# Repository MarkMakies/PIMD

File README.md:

# PIMD — Pulse Induction Metal Detector

*A from-scratch, multi-band pulse-induction metal detector built for autonomous, position-tagged ground survey.*

> Above: a single live frame with a steel spanner **and** a copper pipe under the coil. The two
> materials separate *spatially* inside the decay-space matrix — non-ferrous (blue) collapses early,
> ferrous (red) persists late. Getting that separation out of a pulse-induction detector is the whole point.

**Up to date Build diary:** <https://makies.com.au/pulse-induction-metal-detector/>

---

## What it is

A pulse-induction (PI) metal detector designed and built from scratch since November 2023 by a maker
with no prior analogue-electronics background. It is **not** a clone — several design choices are
deliberately unconventional.

In the language of the field, it's a **low-cost, monostatic time-domain electromagnetic (TEM)
spectrometer doing cued interrogation** — though it started life as nothing more ambitious than
"let's build a metal detector with no experience." It is one payload of a larger system: the coil is
towed on a trailer behind **Roverling**, an autonomous RTK-GPS ground robot, so every detection event
can be tagged with centimetre-level position and streamed back over LoRa. It therefore has to be
*quiet, stable and remotely controllable*, not merely sensitive.

What makes it unusual among PI detectors is that it doesn't optimise a single operating point.
It cycles through a user-defined grid of operating points and reports, for every frame, a
two-dimensional **decay-space matrix** — frequency/pulse-width on one axis, decay-amplitude (time) on
the other — that is designed from the ground up as an input to a classifier.

## How it works (in brief)

A high-current pulse energises the TX coil; on hard cutoff the collapsing field produces a flyback
and then a decaying eddy-current response. A nearby target perturbs that decay. The conditioned RX
signal is sampled at precise, calibrated delays.

- **Mode 1** — a single filtered (32-bit) sample at one held delay: the low-noise telemetry path, used for baselines and field tests.
- **Mode 2** — an interleaved sweep across a profile of *(frequency, pulse-width, sample-delay)* points, reported as one frame per sweep. The grid is not fixed by the hardware, and it has deliberately *narrowed* as the corpus taught which cells earn their place. The July 2026 signature corpus was captured on a **63-cell** grid (7 pulse widths × 9 delays, spaced geometrically 9 → 100 µs at ×1.5 per step). The **current profile, `cal_2x11_v5`, runs 2 pulse widths (10 and 100 µs) × 11 sample delays = a 22-cell matrix**, sweeping at **16.1 Hz** *(measured)* — ~30% faster frames for the loss of the redundant middle bands. It is **not yet locked and has no corpus behind it**. Repetition rates are chosen to hold duty near 30%; the 100 µs band runs at 3.125 kHz and **requires the cooling fan** (see Hardware).
- Sample delays use **two anchoring schemes in one profile**, where a PI profile conventionally picks one. Early cells are **amplitude-anchored** to a ladder of voltages (**2.4 V → 125 mV**) high on the flyback decay rather than the usual bottom ~700 mV — that region carries the most discrimination information, and it is where target *polarity* separates the families. Late cells are **time-anchored** on a geometric ladder out along the tail, because past the front end's lobe both families read positive and only *decay rate* separates them. Every delay is snapped to the 8 ns PWM grid (off-grid requests are silently rounded by the hardware). The profile spans the decay from 2.4 V down to the ~110 mV pedestal with no gaps — the null minimum is sampled deliberately, not avoided.
- **Polarity convention:** ferrous targets read **positive** (stored magnetic energy reinforces the decay); non-ferrous read **negative** (opposing eddy currents weaken it). A third class turns out to be common in practice: **crossover targets** (cast iron, some stainless, real jewelry with steel fittings) read negative at short pulses and positive at long ones — the pulse-width axis resolves what a single operating point would misclassify.

## Highlights

- A multi-band decay-space matrix recovering **multi-time-constant discrimination from a PI platform** — something most commercial PI detectors don't attempt.
- **Validated on a 17-target labelled corpus** (July 2026): signature *shape* is invariant with target distance (5–15 cm, 30× amplitude range) and repeats across sessions and recalibrations to within a few percent — the property the classification layer is built on.
- Targets fall into **three shape families** — ferrous, non-ferrous, and crossover — and overlapping targets combine **linearly** (a spanner + copper pipe frame decomposes back into its parts at 0.99 correlation), so unmixing is on the table, not just classification.
- Phase-locked TX/sample timing on one RP2040 PWM slice — **~5 ns sample-trigger jitter (measured)**.
- LTC2508-32 dual-output front end (filtered 32-bit + raw 14-bit no-latency).
- A dedicated delay-calibration tool that measures the clip-release point per band and exports calibrated profiles.
- Three PyQt6 desktop tools: live Mode 1 GUI, the Mode 2 heatmap + ML-data bridge (`ClassViz`, including a self-describing session recorder for training data), and the delay calibrator.
- Built for autonomous use: RTK-GPS position tagging, LoRa telemetry, single dedicated low-noise supply.

## Repository layout

```
README.md                  This file — start here
DESIGN.md                  Full engineering reference (hardware, firmware, protocol, test log)
CHANGELOG.md               Project change log
CLAUDE.md                  Contributor / agent conventions (version bumps, changelog discipline)

mcu/                       MicroPython firmware for the RP2040-Zero
  pimd_mcu.py  main.py

src/                       PC-side tools (PyQt6)
  pimd_gui.py              Mode 1 filtered-telemetry GUI
  pimd_classviz.py         Mode 2 decay-space heatmap + ML logger
  pimd_delaycal.py         Delay-calibration sweep tool
  pimd_rawlog.py           Raw Mode 2 session logger
  pimd_pack.py             Shared 6S pack fuel-gauge maths (imported by the four GUI apps)
  pimd_shape.py            Shared feature maths (family / crossing / decay persistence)
  pimd_features.py         Training-corpus builder
  pimd_target_check.py     Target-registry validator
  pimd_corpus_check.py     Corpus-level acceptance checker
  requirements.txt
  data/                    Settings, captured CSVs and calibrated profiles (runtime-generated)

Electronics/PIMD604/       KiCad project — schematic rev 6.04 (as-built)

References/                Schematic export, scope captures, sample heatmaps
```

## Toolchain & workflow

The firmware is the measurement primitive; every PC tool is a client of the same USB-serial
protocol (`DESIGN.md` §9). Together they form one pipeline:

```
mcu/pimd_mcu.py (RP2040)            — the measurement primitive
      │  USB-serial, ASCII records (DESIGN §9)
      ├─► src/pimd_delaycal.py      — calibrates sample delays,
      │        exports cal_*.json profiles ──► src/data/profiles/
      ├─► src/pimd_gui.py           — Mode 1 live telemetry / bench monitor
      ├─► src/pimd_rawlog.py        — verbatim Mode 2 session logger (ground truth)
      └─► src/pimd_classviz.py      — Mode 2 heatmap; loads & runs saved profiles;
               │    captures signatures ──► src/data/corpora/ + src/data/sessions/
               └─ uses src/pimd_shape.py — shared feature maths
                            │
                            ▼
          src/pimd_features.py + src/pimd_target_check.py
               — registry-validated training-corpus builder ──► ML corpus
```

`pimd_pack.py` is shared by all four GUI apps, so they can never disagree about the same battery.

**Typical workflow**

1. Flash the firmware once (`DESIGN.md` §16).
2. Run **delaycal** after a full thermal soak to produce a calibrated profile; lock the profile JSON.
3. Run **classviz**, *Load & Run* the locked profile, and capture target signatures against the
   target registry in `src/data/targets/`.
4. Build the corpus with **features**; gate a capture day with **corpus_check**.

**gui** is the independent Mode 1 bench monitor used for noise-floor and drift investigation at a
single operating point. **rawlog** is the deliberately dumb recorder: it writes every line the
firmware sends, verbatim, so there is always a raw record no display logic can corrupt. Never run
Mode 1 and Mode 2 at once — always send `E` between mode switches.

> Each tool carries its own detailed operating notes — intent, wire commands used, record formats
> and per-version lineage — in its **file header**, which is updated in the same edit that changes
> the behaviour. Current firmware and tool versions, and the operating profile in use, are on the
> header line at the top of **`DESIGN.md`**; they are deliberately not duplicated here.

## Quick start

No build step for either the PC tools or the firmware.

### PC tools

```bash
python3 -m venv .venv && source .venv/bin/activate
pip install -r src/requirements.txt
cd src
python pimd_gui.py        # Mode 1 GUI (filtered telemetry)
python pimd_classviz.py   # Mode 2 decay-space visualiser + ML bridge
python pimd_delaycal.py   # delay-calibration sweep
```

The tools connect to the board on `/dev/ttyACMx` at 115200 baud.

### Firmware

```bash
# No build step — copy onto the board, then power-cycle it.
.venv/bin/mpremote connect /dev/ttyACM0 fs cp mcu/pimd_mcu.py :pimd_mcu.py + fs cp mcu/main.py :main.py
# (mpremote reset does not re-enumerate USB reliably — power-cycle the board.)
.venv/bin/mpremote connect /dev/ttyACM0 repl
```

### Bench-test over a serial terminal (115200)

```
V                              identify / firmware version
L                              list profiles
Q5   then  G                   Mode 2: stream the loaded operating profile (W5 records);  E to stop
*5000,40000,8400,256  then S   Mode 1: stream (* records, ~20/s);  E to stop
A32                            one 32-sample boxcar average (R record)
```

> Protocol note (firmware v4.23+): the `*` command takes **freq in Hz, pulse/delay in ns**; the `D`
> dynamic-profile command takes **µs**. See `DESIGN.md` §9 for the full contract.

## Hardware

- **Schematic:** the published KiCad project is **rev 6.04**, which represents the board **as-built**. The PCB itself was fabricated from rev **6.01**; 6.04 captures the corrections — there were a few PCB issues that needed rectifying after manufacture.
- **Front end / drive:** functional but a known rework target — a future revision will replace the TX switch and gate driver (planned: STP10NM60N + TC4420/TC4429) to retire the current FET being run past its rated SOA.
- **Thermal:** a thermistor is now fitted to the TX damping resistor. Thermal drift settles to effectively zero once the resistor reaches ~80 °C, which is the dominant warm-up transient.

## Roadmap

This release is **Phase 2 — publish the work to date.** Active and planned work:

- **Phase 3 — machine learning.** Use the decay-space matrix for filtering, classification and (the stretch goal) ground discrimination. First milestone reached (July 2026): a locked, delay-calibrated operating profile and a 17-target labelled signature corpus recorded at three distances, with distance-invariance, cross-session repeatability and mixture linearity all verified in air.
- **Faster response.** First cut made (August 2026): 63 cells → 22, for ~30% faster sweeps. Because the corpus says different targets go redundant in *different* cells, the narrowed grid has to earn its keep against a fresh corpus before it can be locked — that re-validation is the open work, along with per-cell averaging.
- **Front-end revision** (TX switch + gate driver, as above), plus a scope measurement of TX coil current vs pulse width to settle whether the longest band is past the coil-current plateau.

See **DESIGN.md §14** for the full open-problems list.

## Documentation

- **[DESIGN.md](DESIGN.md)** — the complete engineering reference: measured operating envelope, coils, drive and receive chains, timing, serial protocol, power, invariants and curated test log. Self-contained; a new reader (human or agent) can pick up the project cold from it.
- **Per-app notes** — each tool's intent, operation, wire commands and version lineage live in its own **file header** (`mcu/pimd_mcu.py`, `src/pimd_*.py`); the pipeline that connects them is under *Toolchain & workflow* above.
- **Build diary** — the full chronological story, with photos and dead-ends: <https://makies.com.au/pulse-induction-metal-detector/>
- **Video** — <https://www.youtube.com/@markmakies>

## Licence

This project uses two licences, matched to the kind of work:

- **Code** (`src/`, `mcu/`) — **GNU GPL v3.0-or-later**. See [`LICENSE`](LICENSE).
- **Hardware and documentation** (`Electronics/`, `DESIGN.md`, schematics, images) — **Creative Commons Attribution-ShareAlike 4.0 (CC BY-SA 4.0)**. See [`LICENSE-docs`](LICENSE-docs).

Pulse Induction Metal Detector © 2022–2026 Mark Makies.

## Author

Built by **Mark Makies** (Australia).
Find more work at <https://makies.au/>.

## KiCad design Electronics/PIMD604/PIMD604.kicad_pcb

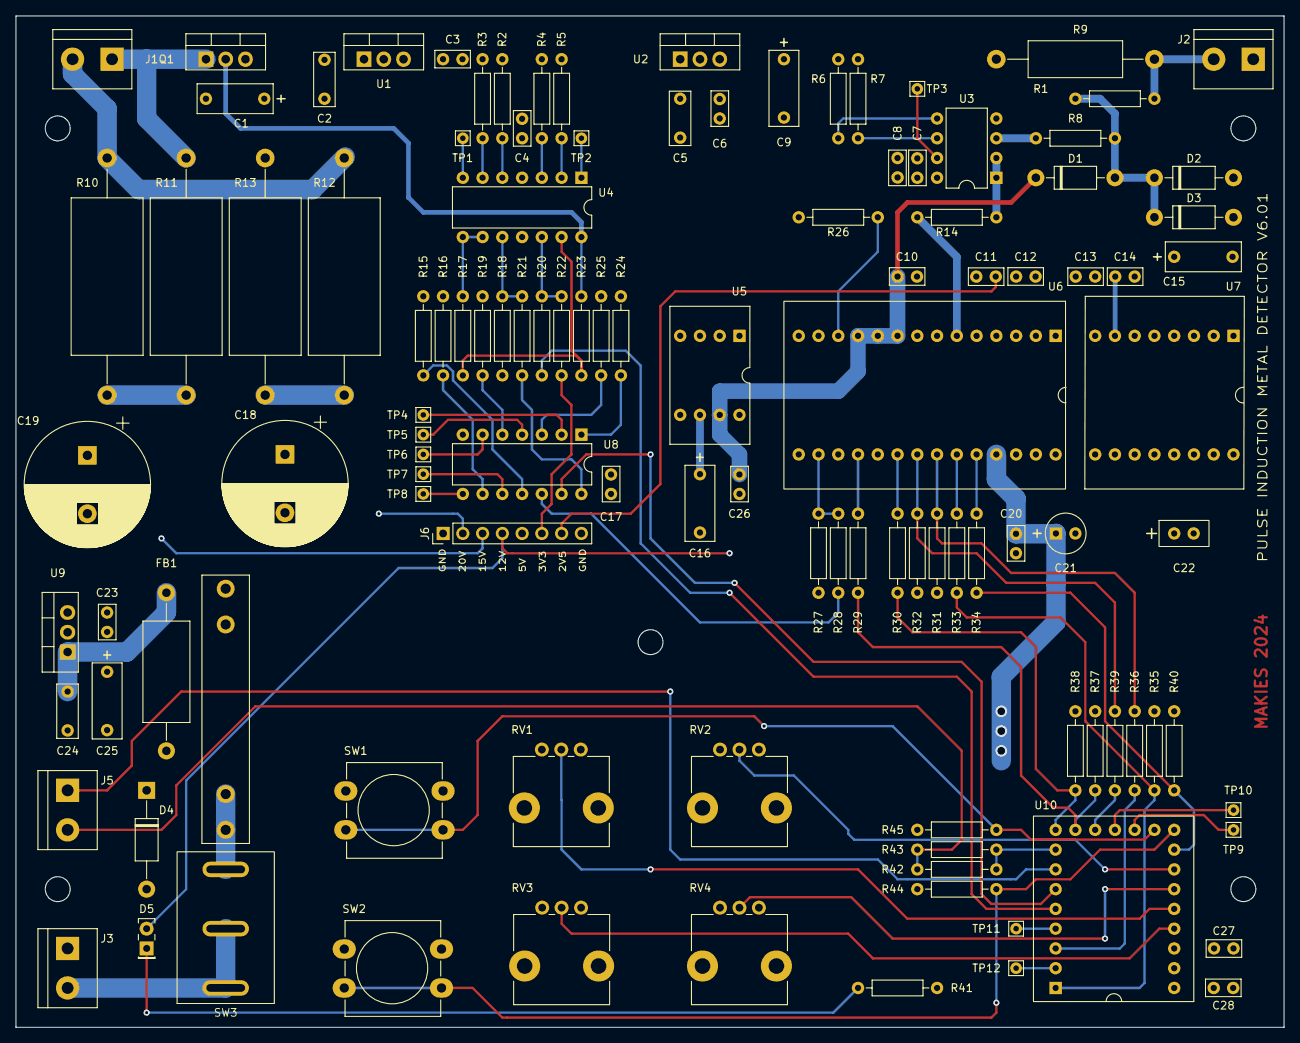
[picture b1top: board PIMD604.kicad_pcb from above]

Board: 4 copper layers, 163.0 x 130.0 mm, 120 parts (0 on the bottom side), 77 nets.

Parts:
C1, C9, C15, C16, C25: 47u; C_Rect_L9.0mm_W3.6mm_P7.50mm_MKT
C2, C5, C24: 220n; C_Disc_D5.0mm_W2.5mm_P5.00mm
C3, C4, C6, C8, C10, C11, C13, C17, C20, C23, C26, C27, C28: 100n; C_Disc_D3.0mm_W2.0mm_P2.50mm
C7, C12, C14: 10n; C_Disc_D3.0mm_W2.0mm_P2.50mm
C18: 2200u; CP_Radial_D16.0mm_P7.50mm
C19: 4700u; CP_Radial_D16.0mm_P7.50mm
C21: 10u; CP_Radial_Tantal_D5.0mm_P2.50mm
C22: 4u7; C_Rect_L7.0mm_W3.5mm_P2.50mm_P5.00mm
D1, D3: 1N5817; D_DO-41_SOD81_P10.16mm_Horizontal
D2: 1N4733; D_DO-41_SOD81_P10.16mm_Horizontal
D4: 1N4004; D_DO-41_SOD81_P12.70mm_Horizontal
D5: LED; LED_Rectangular_W5.0mm_H2.0mm
F1: 2A; Fuseholder_Littelfuse_100_series_5x30mm
FB1: FerriteBead_Small; L_Axial_L12.8mm_D5.8mm_P20.32mm_Horizontal_Fastron_HBCC
H1, H2, H3, H4, H5: MountingHole; MountingHole_3.2mm_M3
J1, J2, J3, J5: Screw_Terminal_01x02; TerminalBlock_bornier-2_P5.08mm
J6: Conn_01x08_Pin; PinHeader_1x08_P2.54mm_Vertical
Q1: IRF610; TO-220-3_Vertical
R1: 1k8; R_Axial_DIN0414_L11.9mm_D4.5mm_P20.32mm_Horizontal
R2, R3, R4, R5, R6, R7, R15, R16, R19, R24, R25, R26: 0R; Resistor
R8, R14: 47R; Resistor
R9, R18, R20, R22, R41: 10k; Resistor
R10: 270R; R_Axial_DIN0922_L20.0mm_D9.0mm_P30.48mm_Horizontal
R11: 220R; R_Axial_DIN0922_L20.0mm_D9.0mm_P30.48mm_Horizontal
R12, R13: 4R7; R_Axial_DIN0922_L20.0mm_D9.0mm_P30.48mm_Horizontal
R17: 4k7; Resistor
R21: 22k; Resistor
R23: 2k7; Resistor
R27, R31, R32, R35, R37, R38, R40: 1k; Resistor
R28, R29, R30, R33, R34, R36, R39: 110R; Resistor
R42, R44, R45: 3k3; Resistor
R43: 43k; Resistor
RV1, RV2, RV3, RV4: 10k; Potentiometer_Alps_RK09L_Single_Vertical
SW1, SW2: SW_MEC_5G; SW_PUSH-12mm_Wuerth-430476085716
SW3: SW_SPDT; SPDT
TP1, TP2, TP3, TP4, TP5, TP6, TP7, TP8, TP9, TP10, TP11, TP12: TestPoint; TestPoint_THTPad_1.5x1.5mm_Drill0.7mm
U1: LM7815; TO-220-3_Vertical
U2: L7812; TO-220-3_Vertical
U3: LT6203; DIP-8_W7.62mm
U4: TL074; DIP-14_W7.62mm
U5: LTC6655-5; DIP-8_W10.16mm
U6: LTC2508-32; DIP-28_W15.24mm
U7: LT1763-2.5; DIP-16_W10.16mm
U8: 74LS04; DIP-14_W7.62mm
U9: LM7805; TO-220-3_Vertical
U10: RP2040-Zero; DIP-24_W10.16mm

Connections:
+2V5: C11.2, C12.2, C13.1, C14.2, C15.1, J6.7, U6.3 (VDD), U7.2 (OUT), U7.3 (OUT), U7.5 (SENSE)
+3V3: C20.2, C21.1, C27.1, J6.6, R22.1, R44.2, R45.2, RV1.1, RV2.1, RV3.1, RV4.1, U6.22 (OVDD), U10.21 (3V3)
+5V: C17.1, C23.2, C25.1, C28.2, J6.5, R21.1, U8.14 (VCC), U9.3 (VO), U10.23 (5V)
+12V: C6.2, C7.2, C8.2, C9.1, C22.1, D5.2 (A), J6.4, U2.3 (OUT), U3.8 (V+), U5.1 (~SHDN), U5.2 (Vin), U7.8 (~SHDN), U7.10 (IN), U7.11 (IN)
+15V: C1.1, C3.2, C19.1, J6.3, R13.1, U1.3 (VO)
+20V: C2.2, C4.1, C5.2, C18.1, D4.1 (K), F1.2, FB1.1, J6.2, U1.1 (VI), U2.1 (IN), U4.4 (V+)
/5V-REF: C10.2, C26.2, D1.1 (K), U5.7 (VOUT-F), U6.8 (REF), U6.9 (REF), U6.10 (REF)
/BUSY: R34.2, R40.1, U10.16 (GP15)
/COIL-DRIVE: R20.1, U10.5 (GP4)
/COMMS-TX: TP9.1, U10.13 (GP12)
/DRL: R29.2, R37.1, U10.10 (GP9)
/MCLK: R27.1, R28.2, U6.13 (MCLK)
/METER-NEG: J5.1, U10.7 (GP6)
/METER-POS: R42.1, R43.1, U10.8 (GP7)
/POT-0: RV3.2, U10.20 (GP29)
/POT-1: RV1.2, U10.19 (GP28)
/POT-2: RV4.2, U10.18 (GP27)
/POT-3: RV2.2, U10.17 (GP26)
/RX-COIL-POS: J2.2, R1.1, R9.2
/SAMPLE: U8.13, U10.6 (GP5)
/SCKA: R32.1, R39.2, U6.18 (SCKA)
/SCKB: R31.1, R36.1, U6.19 (SCKB)
/SDOA: R30.2, R38.1, U10.9 (GP8)
/SDOB: R33.2, R35.1, U10.1 (GP0)
/SW-0: R44.1, SW2.1 (A), U10.15 (GP14)
/SW-1: R45.1, SW1.1 (A), U10.14 (GP13)
/TX-COIL-NEG: J1.1, Q1.1 (D), R11.2
/TX-COIL-POS: J1.2, R10.1, R12.2
GND: C1.2, C2.1, C3.1, C4.2, C5.1, C6.1, C7.1, C8.1, C9.2, C10.1, C11.1, C12.1, C13.2, C15.2, C16.2, C17.2, C18.2, C19.2, C20.1, C21.2, C22.2, C23.1, C24.1, C25.2, C26.1, C27.2, C28.1, D2.2 (A), D3.2 (A), D4.2 (A), J2.1, J3.1, J6.1, J6.8, Q1.3 (S), R1.2, R2.1, R3.1, R4.1, R5.1, R6.1, R7.1, R15.2, R16.2, R18.2, R19.2, R24.2, R25.2, R26.1, R27.2, R31.2, R32.2, R35.2, R37.2, R38.2, R40.2, R41.2, RV1.3, RV2.3, RV3.3, RV4.3, SW1.2 (B), SW2.2 (B), U1.2 (GND), U2.2 (GND), U3.4 (V-), U4.11 (V-), U5.3 (GND), U5.4 (GND), U5.5 (GND), U5.8 (GND), U6.1 (RDLA), U6.2 (RDLB), U6.4 (GND), U6.6 (IN-), U6.7 (GND), U6.12 (SEL1), U6.14 (SYNC), U6.16 (GND), U6.23 (GND), U6.24 (GND), U6.25 (EPAD), U6.26 (EPAD), U6.27 (EPAD), U6.28 (EPAD), U7.7 (GND), U7.13 (GND), U7.14 (GND), U7.15 (GND), U7.16 (GND), U8.7 (GND), U9.2 (GND), U10.22 (GND)
unnamed: D1.2 (A), D2.1 (K), D3.1 (K), R8.1, R9.1
unnamed: D5.1 (K), R41.1
unnamed: J3.2, SW3.1 (A), SW3.2 (B)
unnamed: J5.2, R42.2, R43.2
unnamed: Q1.2 (G), R23.2, U4.14
unnamed: R10.2, R11.1
unnamed: R12.1, R13.2
unnamed: R15.1, U8.11
unnamed: R16.1, U8.9
unnamed: R19.1, U8.5
unnamed: R24.1, U8.1
unnamed: R25.1, U8.3
unnamed: R28.1, U8.12
unnamed: F1.1, SW3.3 (C)
unnamed: TP1.1, U4.7
unnamed: TP2.1, U4.1
unnamed: TP3.1, U3.7
unnamed: TP4.1, U8.2
unnamed: TP5.1, U8.4
unnamed: TP6.1, U8.6
unnamed: TP7.1, U8.10
unnamed: TP8.1, U8.8
unnamed: R8.2, U3.3 (+)
unnamed: R14.1, U3.1, U3.2 (-)
unnamed: R6.2, U3.5 (+)
unnamed: R7.2, U3.6 (-)
unnamed: R4.2, U4.3 (+)
unnamed: R5.2, U4.2 (-)
unnamed: R2.2, U4.5 (+)
unnamed: R3.2, U4.6 (-)
unnamed: R18.1, R21.2, U4.10 (+)
unnamed: R17.1, U4.8, U4.9 (-)
unnamed: R20.2, R22.2, U4.12 (+)
unnamed: R17.2, R23.1, U4.13 (-)
unnamed: C16.1, U5.6 (NR)
unnamed: R34.1, U6.21 (BUSY)
unnamed: R29.1, U6.15 (DRL)
unnamed: R14.2, U6.5 (IN+)
unnamed: R30.1, U6.17 (SDOA)
unnamed: R33.1, U6.20 (SDOB)
unnamed: R26.2, U6.11 (SEL0)
unnamed: C14.1, U7.6 (BYP)
unnamed: C24.2, FB1.2, U9.1 (VI)
unnamed: TP12.1, U10.2 (GP1)
unnamed: R36.2, U10.3 (GP2)
unnamed: TP11.1, U10.4 (GP3)
unnamed: R39.1, U10.11 (GP10)
unnamed: TP10.1, U10.12 (GP11)

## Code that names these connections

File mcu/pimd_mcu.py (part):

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# Runs on RP2040 dev board (Waveshare RP2040-Zero, MicroPython)
#
# Interfaces to LTC2508-32 ADC:
#   SPI1 / filtered 32-bit (SDOA/SCKA/DRL, GPIO8/10/9)  — Mode 1
#   SPI0 / raw 14-bit     (SDOB/SCKB/BUSY, GPIO0/2/15)  — Mode 2
#   1-Wire / DS18B20 board temperature (DQ, GPIO6)      — both modes, v4.33
#
# Mode 1  — filtered/interrupt-driven acquisition
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print('On RP2040 Waveshare RP2040-Zero, ID: ' + board_id_hex)

# ---------------------------------------------------------------------------
# PWM — drive (GPIO4 = PWM2A) and sample-trigger (GPIO5 = PWM2B), same slice
# ---------------------------------------------------------------------------
drive_coil_pwm = PWM(Pin(4))
drive_coil_pwm.freq(10000)
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# ADC interfaces
# ---------------------------------------------------------------------------
# Raw 14-bit, no latency (SPI0)
sckb_pin = Pin(2, Pin.OUT)
sdob_pin = Pin(0, Pin.IN)
busy_pin = Pin(15, Pin.IN)
adc_raw_spi = SPI(0, baudrate=10_000_000, sck=sckb_pin, miso=sdob_pin)

# Filtered 32-bit, decimated (SPI1)
scka_pin = Pin(10, Pin.OUT)
sdoa_pin = Pin(8, Pin.IN)
drl_pin = Pin(9, Pin.IN)
adc_filtered_spi = SPI(1, baudrate=10_000_000, sck=scka_pin, miso=sdoa_pin)

ltc2508_sel0 = Pin(12, Pin.OUT)

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# DS18B20 board temperature — 1-Wire on GP6 (v4.33)
# ---------------------------------------------------------------------------
# GP6 was reserved for a panel meter that is not being fitted. It is free of every
# timing-critical function: the drive/sample PWM pair is GPIO4/5 on slice 2 (DESIGN
# §11), and GP6 is slice 3 used here as a plain open-drain GPIO, so the same-slice
# phase-locking invariant is untouched.
#
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# ---------------------------------------------------------------------------
# Pack-voltage sensing + low-voltage failsafe (v4.28)
# ---------------------------------------------------------------------------
ADC_OVERSAMPLE_N = 64          # raw ADC reads averaged per pack-voltage sample
SENSOR_SAMPLE_MS = 1000        # pack re-sampled + failsafe re-checked, 1 Hz. Board temp
                               # is NOT on this cadence — see DS18B20_INTERVAL_MS.
SENSOR_REPORT_MS = 60_000      # 'P' telemetry line emitted this often
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def acquire_filtered_data():
    global current_filtered_value, drl_ready
    drl_ready = False
    drl_pin.irq(trigger=Pin.IRQ_FALLING, handler=filtered_data_callback)
    while not drl_ready:
        sleep_ms(1)
    data_bytes = adc_filtered_spi.read(4)
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                        # with the signal means the gate is fighting real signal and
                        # OUTLIER_GATE_FRAC is too tight for the profile in use.
busy_timeout_count = 0  # DIAGNOSTIC (v4.37): times a read_raw_bytes_hold() spin hit
                        # BUSY_SPIN_LIMIT and abandoned the sample. Answers the
                        # question the 2026-08-12 outage could not be asked — "did
                        # this happen" — instead of leaving it to be reconstructed
                        # from a truncated session log. Read out via 'B'.
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    """Read one signed 14-bit raw sample from SDOB over SPI0."""
    global busy_high_count
    irq_state = disable_irq()      # keep USB IRQs out of the BUSY-poll + SPI window
    while not busy_pin.value():   # wait for MCLK to fire (BUSY high)
        pass
    busy_high_count += 1
    while busy_pin.value():        # wait for conversion complete (BUSY low)
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    CDC down with it and silenced the board completely — including the
    'PACK: rail absent' message the failsafe exists to print.

    The two spins are not symmetric. Spin 1 waits for the next MCLK trigger: up
    to a full PWM period, times the ~6 windows the poll misses (DESIGN §7), so it
    is the long variable one, it is where nearly all iterations are spent, and it
    is the only one whose margin is worth tracking. Spin 2's wait is
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    global busy_high_count, _held_irq, _busy_spin_left, busy_timeout_count
    _held_irq = disable_irq()
    n = BUSY_SPIN_LIMIT
    while not busy_pin.value():   # wait for MCLK to fire (BUSY high)
        n -= 1
        if not n:
            busy_timeout_count += 1
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def set_safe_state():
    drive_coil_pwm.duty_u16(0)
    sample_coil_pwm.duty_u16(2 ** 16 - 1)
    drl_pin.irq(handler=None)
    print('SAFE: Drive OFF / Sampling OFF / Interrupts OFF')


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
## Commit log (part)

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2026-06-14 Initial commit: PIMD rev 6.01 / fw v3.02 baseline
    Includes Task 1 (ISR refactor + duty-cycle bounds validation) and Task 2
    (raw-path SDOB acquisition primitive, A<x> command/R record, GUI raw-avg
    status display) firmware/GUI changes already applied this session.
2026-06-15 Task 3 step 1: add V/v/? identify command
    Reports firmware version, board ID, profile count, active profile
    index, and the current held configuration. Pure observability, no
    behaviour change to existing *, S, E, A<x> commands.
2026-06-15 Task 3 step 2: add compiled PROFILES table and L command
    PROFILES holds FAST_TRACK (5kHz, single point, x=8) and CLASSIFY
    (10kHz, 3 pulse widths x 8 log-spaced delays, x=32) per Appendix A's
    recommended grid. L lists each profile's index, frequency, grid shape,
    averages-per-point, and name. P<n> is not yet implemented (data only).
2026-06-15 Task 3 step 3: implement P<n> profile runner
    Generic handler validates every (pulse, delay) point in the profile
    against the period budget, runs the z x y grid via run_profile()
    (reprogramming PWM and boxcar-averaging x raw samples per point),
    restores the held configuration, and streams one M<idx> record.
    Bench-verified against profile 0 (FAST_TRACK): M0's mean/std match
    A8 at the same config exactly, and the held config round-trips.
2026-06-15 Task 4 step 1: add SCOPE_CAL profile + reject P<n> while S running
    Bumps FW to 3.03. Adds Profile 2 (SCOPE_CAL): 5kHz, 10us pulse, the
    same 8 log-spaced delays as CLASSIFY, x=1 (single raw sample per
    delay) for oscilloscope-correlated timing checks - no new
    validate/run/M<idx> logic needed, the Task 3 machinery is already
    generic over any z*y*x grid.
    Also rejects P<n> with Command Input ERROR while S telemetry is
2026-06-15 Task 4 step 2: add standalone Scope-Cal Visualiser app (v0.1)
    New src/pimd_scope_cal.py: polls scan Profile 2 (SCOPE_CAL, fw v3.03)
    via P2/M2 every 250ms and plots all 8 delay-channel readings live in
    8 stacked, independently auto-scaling subplots (matplotlib embedded
    in PyQt6), so live data can be correlated against an oscilloscope
    trace of the TX pulse / sample trigger. Sends E on connect, mirrors
    pimd302.py's QSerialPort/connect/status-bar patterns.
2026-06-16 starting /clean
2026-06-17 now maintaining CHANGELOG
2026-06-17 still working on sweep stddev, next dynamic profiles
2026-06-17 snapshot
2026-06-18 rax/filtered now match, moving onto matrix/profiles
2026-06-20 stable but need more decimal places out of gui
2026-06-20 add CLAUDE.md and MM-NOTES.md
2026-06-20 MCU v4.23 / GUI v4.11: serial protocol — freq Hz, pulse/delay ns
    * record, R record, V response, L response: freq now integer Hz (was
    kHz to 1 d.p.), pulse and delay now integer ns (was µs to 1 d.p.).
    No decimal points — values are exact at 8 ns PWM grid resolution.
    * config command format updated to match (GUI sends Hz,ns,ns).
    GUI title standardised to 'PIMD GUI v<N> by Mark Makies'.
2026-06-22 Repo cleanup and licenses, getting ready for GitHub upload Please enter the commit message for your changes. Lines starting
2026-06-24 Revise status in README
    Updated project status and license information in README.
2026-06-24 Update author information in README
2026-06-24 Stop tracking session settings; add coil photos; sync README

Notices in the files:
mcu/pimd_mcu.py:
SPDX-License-Identifier: GPL-3.0-or-later
Copyright (c) 2022-2026 Mark Makies
